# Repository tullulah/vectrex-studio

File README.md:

# Vectrex Studio

A complete development environment for the [Vectrex](https://en.wikipedia.org/wiki/Vectrex) console (Motorola 6809).

---

## What is this?

Vectrex Studio lets you write games for the Vectrex in **VPy**, a Python-like high-level language, and run them instantly in an embedded emulator.

**Components:**
- **VPy compiler** — 9-phase pipeline (Rust) from `.vpy` source to Vectrex ROM
- **Native MC6809 assembler** — built-in, no external tools required
- **IDE** — Electron + React + Monaco editor with LSP (completions, hover, diagnostics, go-to-def, semantic tokens)
- **Emulator** — custom JSVecX embedded in the IDE panel
- **MCP server** — debugger observability tools for AI assistants
- **Asset pipeline** — `.vec` (vectors), `.vmus` (music), `.vsfx` (sound effects)

---

## Quick Start

**Prerequisites:**
- Rust 1.70+ ([install](https://rustup.rs/))
- Node.js 18+ ([install](https://nodejs.org/))
- Vectrex BIOS (8KB) placed at `ide/frontend/public/bios.bin`

**Build and launch:**

```bash
# 1. Build the VPy compiler (vpy_cli) and language server (vpy_lsp)
cargo build --release --bin vpy_cli --bin vpy_lsp

# 2. Install IDE dependencies
cd ide/frontend && npm install
cd ../electron && npm install
cd ../..

# 3. Launch IDE (builds vpy_cli + vpy_lsp and copies them into ide/electron/resources/)
./run-ide.sh        # or: pwsh ./run-ide.ps1
# Or manually: cd ide/frontend && npm run dev, then cd ../electron && npm start
```

**Compile from the command line:**

```bash
./target/release/vpy_cli build examples/pong/pong.vpyproj -o pong.bin
# Options: --target m6809|rp2350|pitrex|uvm2  --debug (emit .pdb)
# Assembly only: vpy_cli asm <file.vpy|project.vpyproj> -o out.asm
```

See [docs/SETUP.md](docs/SETUP.md) for full step-by-step instructions.

---

## Documentation

| Doc | Description |
|-----|-------------|
| [docs/START_HERE.md](docs/START_HERE.md) | Where to go depending on your goal |
| [docs/SETUP.md](docs/SETUP.md) | Full installation and build guide |
| [docs/MANUAL.md](docs/MANUAL.md) | VPy language reference |
| [docs/COMPILER_STATUS.md](docs/COMPILER_STATUS.md) | Compiler phase status and roadmap |
| [docs/INDEX.md](docs/INDEX.md) | Full documentation index |

---

## What Works

### Compiler
- Full VPy language: functions, loops, conditionals, arithmetic, bitwise ops
- 100+ MC6809 opcodes with all addressing modes
- Multibank ROM support (up to 4MB)
- Optimizations: constant folding, dead code elimination, peephole
- Debug symbol generation (`.pdb` files)
- Project format: `.vpyproj` (TOML)

### IDE
- Monaco editor with full LSP: completions, hover, go-to-definition, semantic tokens, diagnostics
- Emulator panel (JSVecX) with Play/Pause/Reset
- Run button: compiles and loads ROM into emulator in one click
- File explorer, error panel, output panel, memory viewer, debug panel
- MCP server for AI assistant integration

### Asset Formats
| Format | Description | Status |
|--------|-------------|--------|
| `.vec` | Vector graphics lists | ✅ Working |
| `.vmus` | Music (PSG AY-3-8912) | ✅ Working |
| `.vsfx` | Sound effects | ✅ Working |
| `.vplay` | Level data | ⏳ Partial |

---

## Project Structure

```
buildtools/     # VPy compiler (Rust, one crate per phase)
  vpy_loader/   # Phase 1 — project file loading (.vpyproj)
  vpy_parser/   # Phase 2 — parsing to AST
  vpy_unifier/  # Phase 3 — multi-file AST unification
  vpy_bank_allocator/  # Phase 4 — multibank ROM allocation
  vpy_codegen/  # Phase 5 — AST to MC6809 assembly
  vpy_assembler/ # Phase 6 — assembly to machine code
  vpy_linker/   # Phase 7 — symbol resolution and linking
  vpy_binary_writer/  # Phase 8 — binary output
  vpy_debug_gen/ # Phase 9 — debug symbol generation
  vpy_cli/      # CLI orchestrator (binary: vpy_cli)
  vpy_lsp/      # Language server (binary: vpy_lsp), same parser as the compiler
ide/            # Electron IDE shell + React frontend
  frontend/     # React/TypeScript UI (Monaco, panels, emulator)
  electron/     # Electron shell
  mcp-server/   # MCP server (Node.js)
emulator/       # Rust emulator crate (not currently used in IDE)
docs/           # All documentation
examples/       # Example VPy programs
```

---

## License

MIT

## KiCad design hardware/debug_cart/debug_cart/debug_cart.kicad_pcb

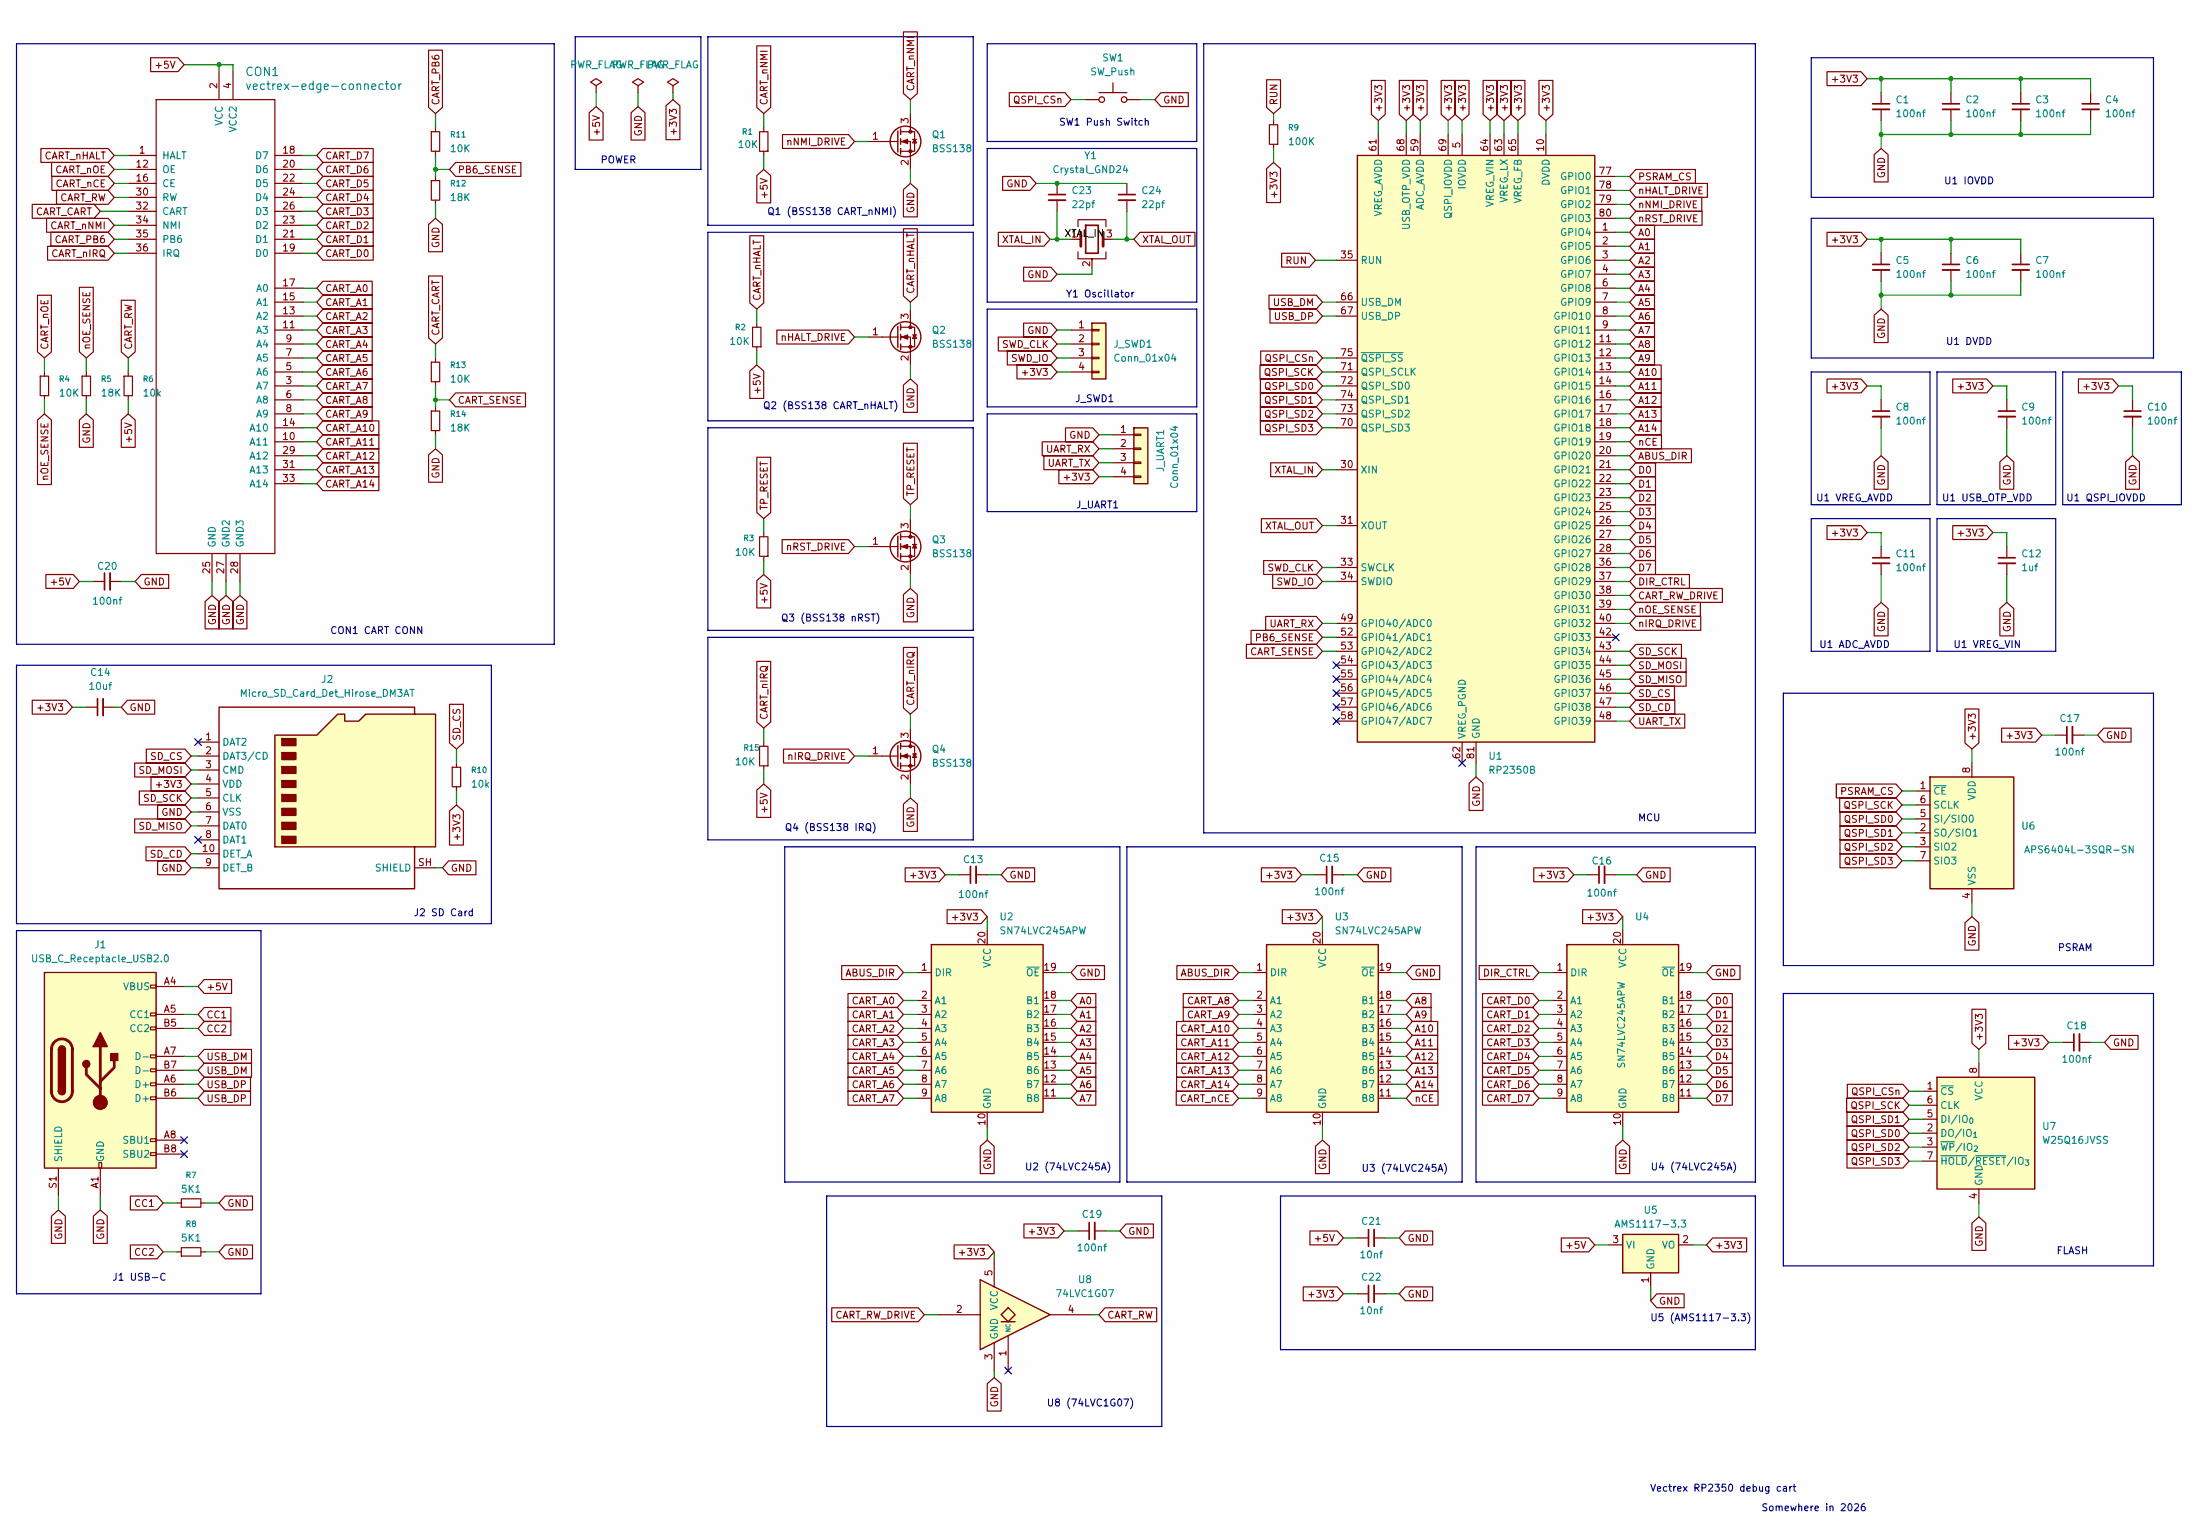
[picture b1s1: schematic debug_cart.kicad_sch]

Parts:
C1, C2, C3, C4, C5, C6, C7, C8, C9, C10, C11, C13, C15, C16, C17, C18, C19, C20: 100nf; C_0603_1608Metric
C12: 1uf; C_0603_1608Metric
C14: 10uf; C_0603_1608Metric
C21, C22: 10nf; C_0603_1608Metric
C23, C24: 22pf; C_0402_1005Metric
CON1: vectrex-edge-connector; vectrex-edge-connector-thinner
J1: USB_C_Receptacle_USB2.0; USB_C_Receptacle_HRO_TYPE-C-31-M-12
J2: Micro_SD_Card_Det_Hirose_DM3AT; microSD_HC_Hirose_DM3AT-SF-PEJM5
J_SWD1: Conn_01x04; PinHeader_1x04_P2.54mm_Vertical
J_UART1: Conn_01x04; PinHeader_1x04_P2.54mm_Vertical
Q1, Q2, Q3, Q4: BSS138; SOT-23
R1, R2, R3, R4, R11, R13, R15: 10K; R_0603_1608Metric
R5, R12, R14: 18K; R_0603_1608Metric
R6, R10: 10k; R_0603_1608Metric
R7, R8: 5K1; R_0603_1608Metric
R9: 100K; R_0603_1608Metric
SW1: SW_Push; SW_SPST_PTS810
U1: RP2350B; QFN-80-1EP_10x10mm_P0.4mm_EP3.4x3.4mm
U2, U3, U4: SN74LVC245APW; TSSOP-20_4.4x6.5mm_P0.65mm
U5: AMS1117-3.3; SOT-223-3_TabPin2
U6: APS6404L-3SQR-SN; SOIC-8_3.9x4.9mm_P1.27mm
U7: W25Q16JVSS; SOIC-8_5.3x5.3mm_P1.27mm
U8: 74LVC1G07; SOT-353_SC-70-5
Y1: Crystal_GND24; Crystal_SMD_3225-4Pin_3.2x2.5mm

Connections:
+3V3: C1.1, C2.1, C3.1, C4.1, C5.1, C6.1, C7.1, C8.1, C9.1, C10.1, C11.1, C12.1, C13.1, C14.1, C15.1, C16.1, C17.1, C18.1, C19.1, C22.1, J2.4 (VDD), J_SWD1.4, J_UART1.4, R9.1, R10.2, U1.5 (IOVDD), U1.10 (DVDD), U1.15 (IOVDD), U1.24 (IOVDD), U1.29 (IOVDD), U1.32 (DVDD), U1.41 (IOVDD), U1.50 (IOVDD), U1.51 (DVDD), U1.59 (ADC_AVDD), U1.60 (IOVDD), U1.61 (VREG_AVDD), U1.63 (VREG_LX), U1.64 (VREG_VIN), U1.65 (VREG_FB), U1.68 (USB_OTP_VDD), U1.69 (QSPI_IOVDD), U1.76 (IOVDD), U2.20 (VCC), U3.20 (VCC), U4.20 (VCC), U5.2 (VO), U6.8 (VDD), U7.8 (VCC), U8.5 (VCC)
+5V: C20.1, C21.1, CON1.2 (VCC), CON1.4 (VCC2), J1.A4 (VBUS), J1.A9 (VBUS), J1.B4 (VBUS), J1.B9 (VBUS), R1.1, R2.1, R3.1, R6.2, R15.1, U5.3 (VI)
A0: U1.1 (GPIO4), U2.18 (B1)
A1: U1.2 (GPIO5), U2.17 (B2)
A2: U1.3 (GPIO6), U2.16 (B3)
A3: U1.4 (GPIO7), U2.15 (B4)
A4: U1.6 (GPIO8), U2.14 (B5)
A5: U1.7 (GPIO9), U2.13 (B6)
A6: U1.8 (GPIO10), U2.12 (B7)
A7: U1.9 (GPIO11), U2.11 (B8)
A8: U1.11 (GPIO12), U3.18 (B1)
A9: U1.12 (GPIO13), U3.17 (B2)
A10: U1.13 (GPIO14), U3.16 (B3)
A11: U1.14 (GPIO15), U3.15 (B4)
A12: U1.16 (GPIO16), U3.14 (B5)
A13: U1.17 (GPIO17), U3.13 (B6)
A14: U1.18 (GPIO18), U3.12 (B7)
ABUS_DIR: U1.20 (GPIO20), U2.1 (DIR), U3.1 (DIR)
CART_A0: CON1.17 (A0), U2.2 (A1)
CART_A1: CON1.15 (A1), U2.3 (A2)
CART_A2: CON1.13 (A2), U2.4 (A3)
CART_A3: CON1.11 (A3), U2.5 (A4)
CART_A4: CON1.9 (A4), U2.6 (A5)
CART_A5: CON1.7 (A5), U2.7 (A6)
CART_A6: CON1.5 (A6), U2.8 (A7)
CART_A7: CON1.3 (A7), U2.9 (A8)
CART_A8: CON1.6 (A8), U3.2 (A1)
CART_A9: CON1.8 (A9), U3.3 (A2)
CART_A10: CON1.14 (A10), U3.4 (A3)
CART_A11: CON1.10 (A11), U3.5 (A4)
CART_A12: CON1.29 (A12), U3.6 (A5)
CART_A13: CON1.31 (A13), U3.7 (A6)
CART_A14: CON1.33 (A14), U3.8 (A7)
CART_CART: CON1.32 (CART), R13.1
CART_D0: CON1.19 (D0), U4.2 (A1)
CART_D1: CON1.21 (D1), U4.3 (A2)
CART_D2: CON1.23 (D2), U4.4 (A3)
CART_D3: CON1.26 (D3), U4.5 (A4)
CART_D4: CON1.24 (D4), U4.6 (A5)
CART_D5: CON1.22 (D5), U4.7 (A6)
CART_D6: CON1.20 (D6), U4.8 (A7)
CART_D7: CON1.18 (D7), U4.9 (A8)
CART_PB6: CON1.35 (PB6), R11.1
CART_RW: CON1.30 (RW), R6.1, U8.4
CART_RW_DRIVE: U1.38 (GPIO30), U8.2
CART_SENSE: R13.2, R14.1, U1.53 (GPIO42/ADC2)
CART_nCE: CON1.16 (CE), U3.9 (A8)
CART_nHALT: CON1.1 (HALT), Q2.3 (D), R2.2
CART_nIRQ: CON1.36 (IRQ), Q4.3 (D), R15.2
CART_nNMI: CON1.34 (NMI), Q1.3 (D), R1.2
CART_nOE: CON1.12 (OE), R4.1
CC1: J1.A5 (CC1), R7.1
CC2: J1.B5 (CC2), R8.1
D0: U1.21 (GPIO21), U4.18 (B1)
D1: U1.22 (GPIO22), U4.17 (B2)
D2: U1.23 (GPIO23), U4.16 (B3)
D3: U1.25 (GPIO24), U4.15 (B4)
D4: U1.26 (GPIO25), U4.14 (B5)
D5: U1.27 (GPIO26), U4.13 (B6)
D6: U1.28 (GPIO27), U4.12 (B7)
D7: U1.36 (GPIO28), U4.11 (B8)
DIR_CTRL: U1.37 (GPIO29), U4.1 (DIR)
GND: C1.2, C2.2, C3.2, C4.2, C5.2, C6.2, C7.2, C8.2, C9.2, C10.2, C11.2, C12.2, C13.2, C14.2, C15.2, C16.2, C17.2, C18.2, C19.2, C20.2, C21.2, C22.2, C23.1, C24.1, CON1.25 (GND), CON1.27 (GND2), CON1.28 (GND3), J1.A1 (GND), J1.A12 (GND), J1.B1 (GND), J1.B12 (GND), J1.S1 (SHIELD), J2.6 (VSS), J2.9 (DET_B), J2.SH (SHIELD), J_SWD1.1, J_UART1.1, Q1.2 (S), Q2.2 (S), Q3.2 (S), Q4.2 (S), R5.2, R7.2, R8.2, R12.2, R14.2, SW1.2, U1.81 (GND), U2.10 (GND), U2.19 (~OE), U3.10 (GND), U3.19 (~OE), U4.10 (GND), U4.19 (~OE), U5.1 (GND), U6.4 (VSS), U7.4 (GND), U8.3 (GND), Y1.2 (G), Y1.4 (G)
PB6_SENSE: R11.2, R12.1, U1.52 (GPIO41/ADC1)
PSRAM_CS: U1.77 (GPIO0), U6.1 (~CE)
QSPI_CSn: SW1.1, U1.75 (~QSPI_SS), U7.1 (~CS)
QSPI_SCK: U1.71 (QSPI_SCLK), U6.6 (SCLK), U7.6 (CLK)
QSPI_SD0: U1.72 (QSPI_SD0), U6.5 (SI/SIO0), U7.2 (DO/IO_{1})
QSPI_SD1: U1.74 (QSPI_SD1), U6.2 (SO/SIO1), U7.5 (DI/IO_{0})
QSPI_SD2: U1.73 (QSPI_SD2), U6.3 (SIO2), U7.3 (~WP/IO_{2})
QSPI_SD3: U1.70 (QSPI_SD3), U6.7 (SIO3), U7.7 (~HOLD/~RESET/IO_{3})
RUN: R9.2, U1.35 (RUN)
SD_CD: J2.10 (DET_A), U1.47 (GPIO38)
SD_CS: J2.2 (DAT3/CD), R10.1, U1.46 (GPIO37)
SD_MISO: J2.7 (DAT0), U1.45 (GPIO36)
SD_MOSI: J2.3 (CMD), U1.44 (GPIO35)
SD_SCK: J2.5 (CLK), U1.43 (GPIO34)
SWD_CLK: J_SWD1.2, U1.33 (SWCLK)
SWD_IO: J_SWD1.3, U1.34 (SWDIO)
TP_RESET: Q3.3 (D), R3.2
UART_RX: J_UART1.2, U1.49 (GPIO40/ADC0)
UART_TX: J_UART1.3, U1.48 (GPIO39)
USB_DM: J1.A7 (D-), J1.B7 (D-), U1.66 (USB_DM)
USB_DP: J1.A6 (D+), J1.B6 (D+), U1.67 (USB_DP)
XTAL_IN: C23.2, U1.30 (XIN), Y1.1
XTAL_OUT: C24.2, U1.31 (XOUT), Y1.3
nCE: U1.19 (GPIO19), U3.11 (B8)
nHALT_DRIVE: Q2.1 (G), U1.78 (GPIO1)
nIRQ_DRIVE: Q4.1 (G), U1.40 (GPIO32)
nNMI_DRIVE: Q1.1 (G), U1.79 (GPIO2)
nOE_SENSE: R4.2, R5.1, U1.39 (GPIO31)
nRST_DRIVE: Q3.1 (G), U1.80 (GPIO3)

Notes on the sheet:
U1 QSPI_IOVDD
U1 DVDD
Q4 (BSS138 IRQ)
PSRAM
POWER
Somewhere in 2026
J_UART1
U3 (74LVC245A)
SW1 Push Switch
U1 USB_OTP_VDD
U2 (74LVC245A)
Vectrex RP2350 debug cart
U1 IOVDD
FLASH
U5 (AMS1117-3.3)
J2 SD Card
U1 ADC_AVDD
Q2 (BSS138 CART_nHALT)
U8 (74LVC1G07)
CON1 CART CONN
U4 (74LVC245A)
U1 VREG_VIN
MCU
Y1 Oscillator
Q3 (BSS138 nRST)
J1 USB-C
J_SWD1
Q1 (BSS138 CART_nNMI)
U1 VREG_AVDD

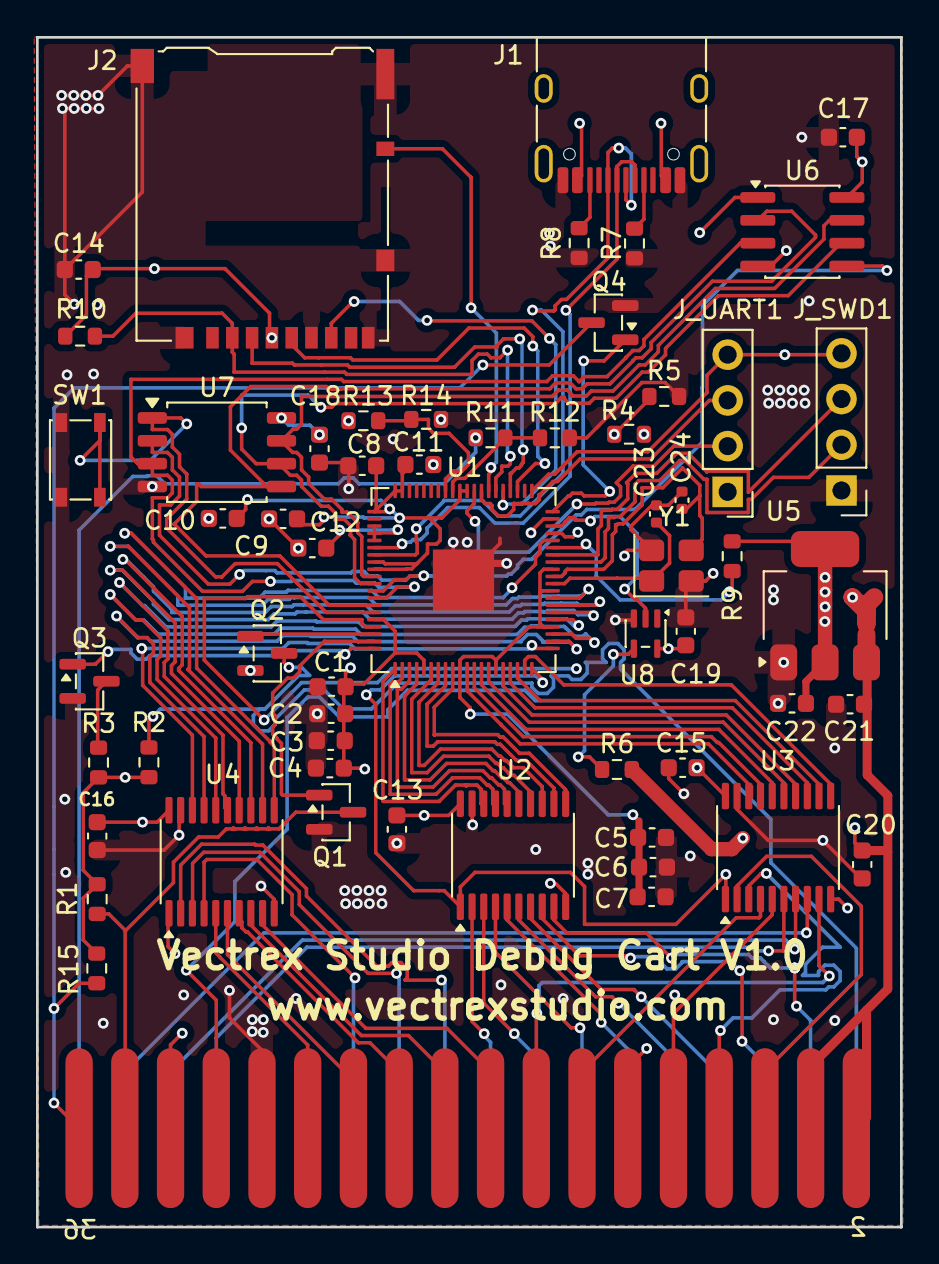
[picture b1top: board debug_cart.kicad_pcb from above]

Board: 4 copper layers, 48.0 x 66.1 mm, 58 parts (0 on the bottom side), 92 nets.

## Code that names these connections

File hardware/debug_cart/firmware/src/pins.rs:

#![allow(dead_code)] // Hardware constants — used by Phase 2+ modules

/// GPIO pin assignments for the Vectrex Debug Cart (RP2350B / PCB v2)
///
/// Layout strategy:
/// RP2350B QFN-80 rotated so SIDE A (pins 1-20, containing GPIO4-20) faces
/// the cartridge edge. This keeps the bus signals (address + /CE + ABUS_DIR)
/// physically close to the buffers U2/U3 and the card-edge connector,
/// minimising trace crossings on a 2-layer PCB.
///
/// QFN-80 sides:
///   - Side A (pins  1-20) ← faces card edge: A0..A14, /CE, ABUS_DIR
///   - Side B (pins 21-40) ← faces data buffer: D0..D7, DIR_CTRL, CART_RW, /OE sense
///   - Side C (pins 41-60) ← faces SD/UART connectors: SD, UART, PB6, CART, IRQ drive
///   - Side D (pins 61-80) ← faces memories + USB: QSPI flash/PSRAM, USB-C, HALT/NMI/RST drives

// ============================================================
// SIDE A — Bus signals facing card edge (via U2, U3 buffers)
// ============================================================

/// Address bus (15 pins → buffers U2 [A0-A7] and U3 [A8-A14])
pub const PIN_A0:  u8 = 4;
pub const PIN_A1:  u8 = 5;
pub const PIN_A2:  u8 = 6;
pub const PIN_A3:  u8 = 7;
pub const PIN_A4:  u8 = 8;
pub const PIN_A5:  u8 = 9;
pub const PIN_A6:  u8 = 10;
pub const PIN_A7:  u8 = 11;
pub const PIN_A8:  u8 = 12;
pub const PIN_A9:  u8 = 13;
pub const PIN_A10: u8 = 14;
pub const PIN_A11: u8 = 15;
pub const PIN_A12: u8 = 16;
pub const PIN_A13: u8 = 17;
pub const PIN_A14: u8 = 18;

/// Cartridge chip enable from U3 B8 (3.3V, no divider needed — buffer level shifts)
pub const PIN_NCE: u8 = 19;

/// Address bus buffer direction (drives U2 pin 1 + U3 pin 1)
/// LOW = Vectrex→RP2350 (ROM read), HIGH = RP2350→Vectrex (bus master write)
pub const PIN_ABUS_DIR: u8 = 20;

/// Bitmasks for address bus GPIO operations
pub const ADDR_LOW_MASK:  u32 = 0x00000FF0;  // GP4–GP11  (A0–A7)
pub const ADDR_HIGH_MASK: u32 = 0x0007F000;  // GP12–GP18 (A8–A14)
pub const ADDR_MASK:      u32 = ADDR_LOW_MASK | ADDR_HIGH_MASK;

// ============================================================
// SIDE B — Data bus + bus control (via U4 buffer + U8 driver)
// ============================================================

/// Data bus (8 pins → buffer U4)
pub const PIN_D0: u8 = 21;
pub const PIN_D1: u8 = 22;
pub const PIN_D2: u8 = 23;
pub const PIN_D3: u8 = 24;
pub const PIN_D4: u8 = 25;
pub const PIN_D5: u8 = 26;
pub const PIN_D6: u8 = 27;
pub const PIN_D7: u8 = 28;

pub const DATA_SHIFT: u8  = 21;                   // D0 starts at GP21
pub const DATA_MASK:  u32 = 0xFF << DATA_SHIFT;   // GP21–GP28

/// Data buffer direction (drives U4 pin 1). LOW = read, HIGH = write.
pub const PIN_DIR_CTRL: u8 = 29;

/// CART_RW drive (drives input of U8 74LVC1G07 open-drain).
/// LOW = U8 high-Z → R6 pulls CART_RW HIGH (read).
/// HIGH = U8 pulls CART_RW LOW (write).
pub const PIN_CART_RW_DRV: u8 = 30;

/// /OE sense from card edge (5V → 3.21V via R4/R5 divider).
pub const PIN_NOE_SENSE: u8 = 31;

/// /IRQ drive (gate of Q4 BSS138 → CON1 pin 36).
/// Last GPIO on side B (corner pin 40 of QFN-80) — close to the BSS138
/// transistor near the card edge.
pub const PIN_NIRQ_DRV: u8 = 32;

// ============================================================
// SIDE C — SD card + UART + vextreme extended signals + IRQ
// ============================================================

/// microSD on SPI0 (Hirose DM3AT-SF push-push)
pub const PIN_SD_SCK:  u8 = 34;
pub const PIN_SD_MOSI: u8 = 35;
pub const PIN_SD_MISO: u8 = 36;
pub const PIN_SD_CS:   u8 = 37;
/// Card-detect: input with internal pullup. LOW = card present.
pub const PIN_SD_CD:   u8 = 38;

/// UART0 hardware (J_UART1 header pinout)
pub const PIN_UART_TX: u8 = 39;
pub const PIN_UART_RX: u8 = 40;

/// VIA 6522 PB6 sense (CON1 pin 35 via R11/R12 divider 5V→3.21V).
/// Comparator output of DAC X — analog beam-cross-zero detection.
pub const PIN_PB6_SENSE: u8 = 41;

/// Vextreme CART signal sense (CON1 pin 32 via R13/R14 divider).
/// Status of Vectrex 74LS32 IC203A OR-gate (address decoder derived signal).
pub const PIN_CART_SENSE: u8 = 42;

// ============================================================
// SIDE D — PSRAM CS + 3 of 4 BSS138 drives
// (side D has only GP0-3 as GPIOs; rest is QSPI/USB/VREG hardware pins)
// ============================================================

/// PSRAM CS — drives U6 (APS6404L) pin 1.
/// Not a QSPI hardware CS — uses QMI direct-mode via GPIO bit-bang.
/// Placed on side D adjacent to the QSPI hardware pins for minimal trace
/// length to U6 (timing-critical at 50+ MHz).
pub const PIN_PSRAM_CS: u8 = 0;

/// GPIO HIGH → BSS138 conducts → 6809 line pulled to GND (signal asserted).
/// GPIO LOW  → BSS138 off → 10kΩ pullup to +5V → signal deasserted.
/// Side D placement: BSS138 transistor physically near card edge, gate trace
/// from MCU is a 3.3V CMOS control signal with no timing/EMI concerns.
pub const PIN_NHALT_DRV: u8 = 1;
pub const PIN_NNMI_DRV:  u8 = 2;
pub const PIN_NRST_DRV:  u8 = 3;
// PIN_NIRQ_DRV is on side B (GP32) — see above

// ============================================================
// Helpers
// ============================================================

/// Helper: build full 32-bit GPIO word for address A (A0–A14 → GP4–GP18)
#[inline(always)]
pub fn addr_to_gpio(addr: u16) -> u32 {
    ((addr as u32) << 4) & ADDR_MASK
}

/// Helper: extract A0–A14 address from GPIO input word
#[inline(always)]
pub fn gpio_to_addr(gpio: u32) -> u16 {
    ((gpio & ADDR_MASK) >> 4) as u16
}

/// Helper: build GPIO word for data byte D0–D7 mapped to GP21–GP28
#[inline(always)]
pub fn data_to_gpio(byte: u8) -> u32 {
    (byte as u32) << DATA_SHIFT
}

/// Helper: extract data byte from GPIO input word
#[inline(always)]
pub fn gpio_to_data(gpio: u32) -> u8 {
    ((gpio >> DATA_SHIFT) & 0xFF) as u8
}

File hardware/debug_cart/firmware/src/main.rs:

//! Vectrex Debug Cart firmware — Phase 1: bringup
//!
//! On startup:
//!   1. Asserts /HALT → 6809 halts and tri-states the bus
//!   2. Initialises USB CDC (serial console at 115200 baud via USB)
//!   3. Tests PSRAM (APS6404L, 8 MB via QSPI) — write/read pattern
//!   4. Prints status to USB serial
//!   5. Enters command loop (echo input, future: 'm' memory dump, 'w' VIA write)
//!
//! Phase 2 (ROM emulation) and Phase 3 (bus master) are guarded behind
//! feature flags until the respective hardware is verified.

#![no_std]
#![no_main]

use panic_halt as _;

use rp235x_hal as hal;
use hal::{
    clocks::Clock,
    pac,
};
use cortex_m_rt::entry;
use embedded_hal::digital::OutputPin;

use usb_device::{class_prelude::*, prelude::*};
use usbd_serial::SerialPort;

mod pins;
mod vectrex_hal;
mod bus;
mod psram;
mod flash;

// RP2350 boot block — replaces RP2040's boot2.
// Tells the bootrom this is a valid secure executable image.
#[link_section = ".start_block"]
#[used]
pub static IMAGE_DEF: hal::block::ImageDef = hal::block::ImageDef::secure_exe();

const XTAL_FREQ_HZ: u32 = 12_000_000;

/// Simple write to USB serial, ignores errors (host may not be connected yet)
pub(crate) fn usb_print<B: usb_device::bus::UsbBus>(
    serial: &mut SerialPort<'_, B>,
    s: &[u8],
) {
    // USB CDC may need multiple writes if buffer is full
    let mut written = 0;
    while written < s.len() {
        match serial.write(&s[written..]) {
            Ok(n) => written += n,
            Err(_) => break,
        }
    }
}

/// Format u32 as decimal into a fixed buffer. Returns slice of used bytes.
#[allow(dead_code)] // used by Phase 2+ command responses
fn fmt_u32(val: u32, buf: &mut [u8; 10]) -> &[u8] {
    let mut n = val;
    let mut i = buf.len();
    if n == 0 {
        buf[9] = b'0';
        return &buf[9..];
    }
    while n > 0 && i > 0 {
        i -= 1;
        buf[i] = b'0' + (n % 10) as u8;
        n /= 10;
    }
    &buf[i..]
}

#[entry]
fn main() -> ! {
    //
    // 1. Peripheral init
    //
    let mut pac  = pac::Peripherals::take().unwrap();
    let core = cortex_m::peripheral::Peripherals::take().unwrap();

    let mut watchdog = hal::Watchdog::new(pac.WATCHDOG);

    // Init PLL: system clock 133 MHz, USB clock 48 MHz
    let clocks = hal::clocks::init_clocks_and_plls(
        XTAL_FREQ_HZ,
        pac.XOSC,
        pac.CLOCKS,
        pac.PLL_SYS,
        pac.PLL_USB,
        &mut pac.RESETS,
        &mut watchdog,
    ).ok().unwrap();

    let mut delay = cortex_m::delay::Delay::new(
        core.SYST,
        clocks.system_clock.freq().to_Hz(),
    );

    let sio  = hal::Sio::new(pac.SIO);
    let gpio = hal::gpio::Pins::new(
        pac.IO_BANK0,
        pac.PADS_BANK0,
        sio.gpio_bank0,
        &mut pac.RESETS,
    );

    //
    // 2. Assert /HALT immediately — 6809 stops within ~7 µs
    //
    // BSS138 FET: GPIO HIGH → gate driven → drain pulled low → /HALT asserted
    let mut nhalt = gpio.gpio27.into_push_pull_output();
    nhalt.set_high().unwrap();

    // NMI and RST idle (not asserted)
    let mut nnmi = gpio.gpio26.into_push_pull_output();
    nnmi.set_low().unwrap();
    let mut nrst = gpio.gpio28.into_push_pull_output();
    nrst.set_low().unwrap();

    // DIR_CTRL for data bus buffer U4: GP29, LOW = Vectrex→RP2350 (read/ROM mode)
    // Start LOW — RP2350 observes bus. Phase 3 (bus master) will drive HIGH to write.
    let mut dir_ctrl = gpio.gpio29.into_push_pull_output();
    dir_ctrl.set_low().unwrap();

    delay.delay_ms(1); // 6809 halts within ~7 µs — 1 ms is generous

    //
    // 3. USB CDC
    //
    let usb_bus = UsbBusAllocator::new(hal::usb::UsbBus::new(
        pac.USB,
        pac.USB_DPRAM,
        clocks.usb_clock,
        true,
        &mut pac.RESETS,
    ));

    let mut serial = SerialPort::new(&usb_bus);

    let mut usb_dev = UsbDeviceBuilder::new(&usb_bus, UsbVidPid(0x2E8A, 0x000A))
        .strings(&[StringDescriptors::default()
            .manufacturer("Vectrex Studio")
            .product("Debug Cart v1")
            .serial_number("0001")])
        .unwrap()
        .device_class(2)   // CDC
        .build();

    // Wait for USB host to enumerate (up to 2 seconds)
    let mut connected = false;
    let mut wait_ms = 0u32;
    while !connected && wait_ms < 2000 {
        if usb_dev.poll(&mut [&mut serial]) {
            if serial.line_coding().data_rate() > 0 {
                connected = true;
            }
        }
        delay.delay_ms(1);
        wait_ms += 1;
    }

    //
    // 4. Banner
    //
    usb_print(&mut serial, b"\r\n");
    usb_print(&mut serial, b"=== Vectrex Debug Cart v1 ===\r\n");
    usb_print(&mut serial, b"RP2350 @ 150 MHz  |  8 MB flash  |  8 MB PSRAM  |  FPU\r\n");
    usb_print(&mut serial, b"/HALT asserted: 6809 stopped.\r\n");
    usb_print(&mut serial, b"\r\n");

    //
    // 5. PSRAM self-test
    //
    usb_print(&mut serial, b"PSRAM test... ");
    let psram_ok = psram::init_and_test(&mut delay);
    if psram_ok {
        usb_print(&mut serial, b"OK (8 MB)\r\n");
    } else {
        usb_print(&mut serial, b"FAIL\r\n");
    }

    //
    // 6. Bus master status
    //
    if bus::BUS_MASTER_AVAILABLE {
        usb_print(&mut serial, b"Bus master: available (CART_RW via U8/R13)\r\n");
    } else {
        usb_print(&mut serial, b"Bus master: NOT available\r\n");
    }

    usb_print(&mut serial, b"\r\nReady. Commands: [r]om-mode  [H]alt  [U]nhalt  [F]lash  [?]help\r\n> ");

    //
    // 7. Command loop
    //
    let mut rx_buf = [0u8; 64];

    loop {
        if usb_dev.poll(&mut [&mut serial]) {
            if let Ok(n) = serial.read(&mut rx_buf) {
                for &b in &rx_buf[..n] {
                    match b {
                        b'?' | b'h' => {
                            usb_print(&mut serial, b"\r\nCommands:\r\n");
                            usb_print(&mut serial, b"  r - enter ROM emulation mode (Phase 2)\r\n");
                            usb_print(&mut serial, b"  H - assert /HALT\r\n");
                            usb_print(&mut serial, b"  U - release /HALT\r\n");
                            usb_print(&mut serial, b"  N - pulse /NMI\r\n");
                            usb_print(&mut serial, b"  R - pulse /RST\r\n");
                            usb_print(&mut serial, b"  F - flash game ROM (32KB max, resets after)\r\n");
                            usb_print(&mut serial, b"> ");
                        }
                        b'H' => {
                            nhalt.set_high().unwrap();
                            usb_print(&mut serial, b"HALT asserted\r\n> ");
                        }
                        b'U' => {
                            nhalt.set_low().unwrap();
                            usb_print(&mut serial, b"HALT released - 6809 running\r\n> ");
                        }
                        b'N' => {
                            nnmi.set_high().unwrap();
                            delay.delay_us(10);
                            nnmi.set_low().unwrap();
                            usb_print(&mut serial, b"NMI pulsed\r\n> ");
                        }
                        b'R' => {
                            nrst.set_high().unwrap();
                            delay.delay_ms(10);
                            nrst.set_low().unwrap();
                            // Re-assert HALT so 6809 doesn't run after reset
                            nhalt.set_high().unwrap();
                            usb_print(&mut serial, b"RST pulsed, HALT re-asserted\r\n> ");
                        }
                        b'r' => {
                            usb_print(&mut serial, b"ROM mode not yet implemented (Phase 2)\r\n> ");
                        }
                        b'F' => {
                            // Flash game ROM over USB CDC.
                            // receive_and_flash resets on success; if we reach here it errored.
                            flash::receive_and_flash(&mut usb_dev, &mut serial);
                            usb_print(&mut serial, b"> ");
                        }
                        b'\r' | b'\n' => {
                            usb_print(&mut serial, b"\r\n> ");
                        }
                        _ => {
                            // Echo character
                            serial.write(&[b]).ok();
                        }
                    }
                }
            }
        }
    }
}
